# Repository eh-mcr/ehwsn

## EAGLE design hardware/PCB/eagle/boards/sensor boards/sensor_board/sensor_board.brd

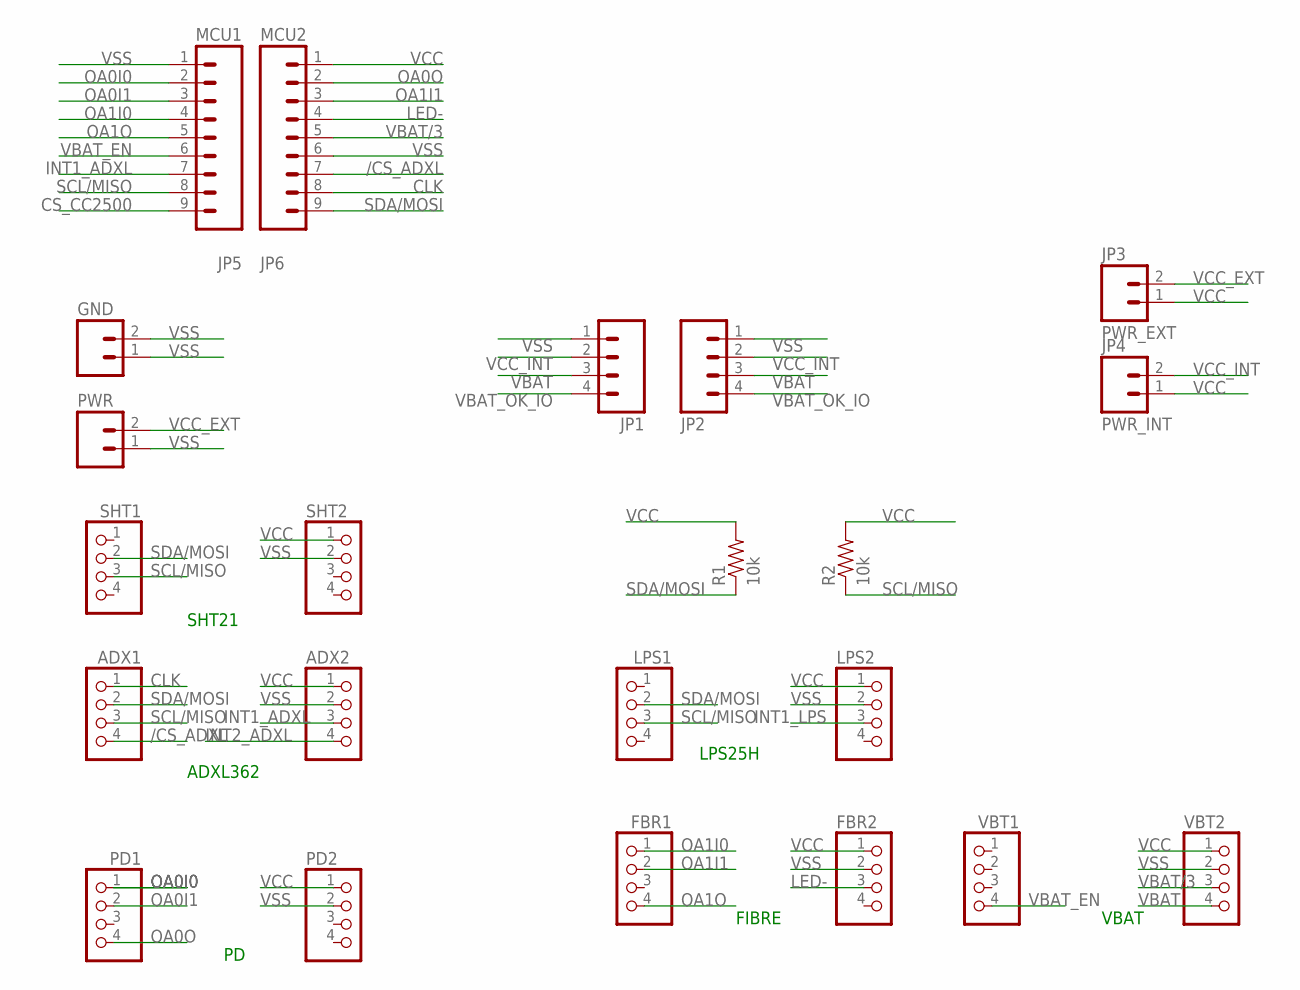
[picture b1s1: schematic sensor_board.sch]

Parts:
ADX1, ADX2: PINHD-1X4; 1X04
FBR1, FBR2: PINHD-1X4; 1X04
GND: M02PTH; 1X02
JP1, JP2: M04PTH; 1X04
JP3: PWR_EXT; 1X02
JP4: PWR_INT; 1X02
JP5: MCU1; 1X09
JP6: MCU2; 1X09
LPS1, LPS2: PINHD-1X4; 1X04
PD1, PD2: PINHD-1X4; 1X04
PWR: M02PTH; 1X02
R1, R2: 10k; AXIAL-0.3
SHT1, SHT2: PINHD-1X4; 1X04
VBT1, VBT2: PINHD-1X4; 1X04

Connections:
/CS_ADXL: ADX1.4, JP6.7
CLK: ADX1.1, JP6.8
CS_CC2500: JP5.9
INT1_ADXL: ADX2.3, JP5.7
INT1_LPS: LPS2.3
INT2_ADXL: ADX2.4
LED-: FBR2.3, JP6.4
OA0I0: JP5.2, PD1.1
OA0I1: JP5.3, PD1.2
OA0O: JP6.2, PD1.4
OA1I0: FBR1.1, JP5.4
OA1I1: FBR1.2, JP6.3
OA1O: FBR1.4, JP5.5
SCL/MISO: ADX1.3, JP5.8, LPS1.3, R2.P$1 (1), SHT1.3
SDA/MOSI: ADX1.2, JP6.9, LPS1.2, R1.P$1 (1), SHT1.2
VBAT: JP1.3, JP2.3, VBT2.4
VBAT/3: JP6.5, VBT2.3
VBAT_EN: JP5.6, VBT1.4
VBAT_OK_IO: JP1.4, JP2.4
VCC: ADX2.1, FBR2.1, JP3.1, JP4.1, JP6.1, LPS2.1, PD2.1, R1.P$2 (2), R2.P$2 (2), SHT2.1, VBT2.1
VCC_EXT: JP3.2, PWR.2
VCC_INT: JP1.2, JP2.2, JP4.2
VSS: ADX2.2, FBR2.2, GND.1, GND.2, JP1.1, JP2.1, JP5.1, JP6.6, LPS2.2, PD2.2, PWR.1, SHT2.2, VBT2.2

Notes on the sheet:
ADXL362
SHT21
LPS25H
FIBRE
VBAT

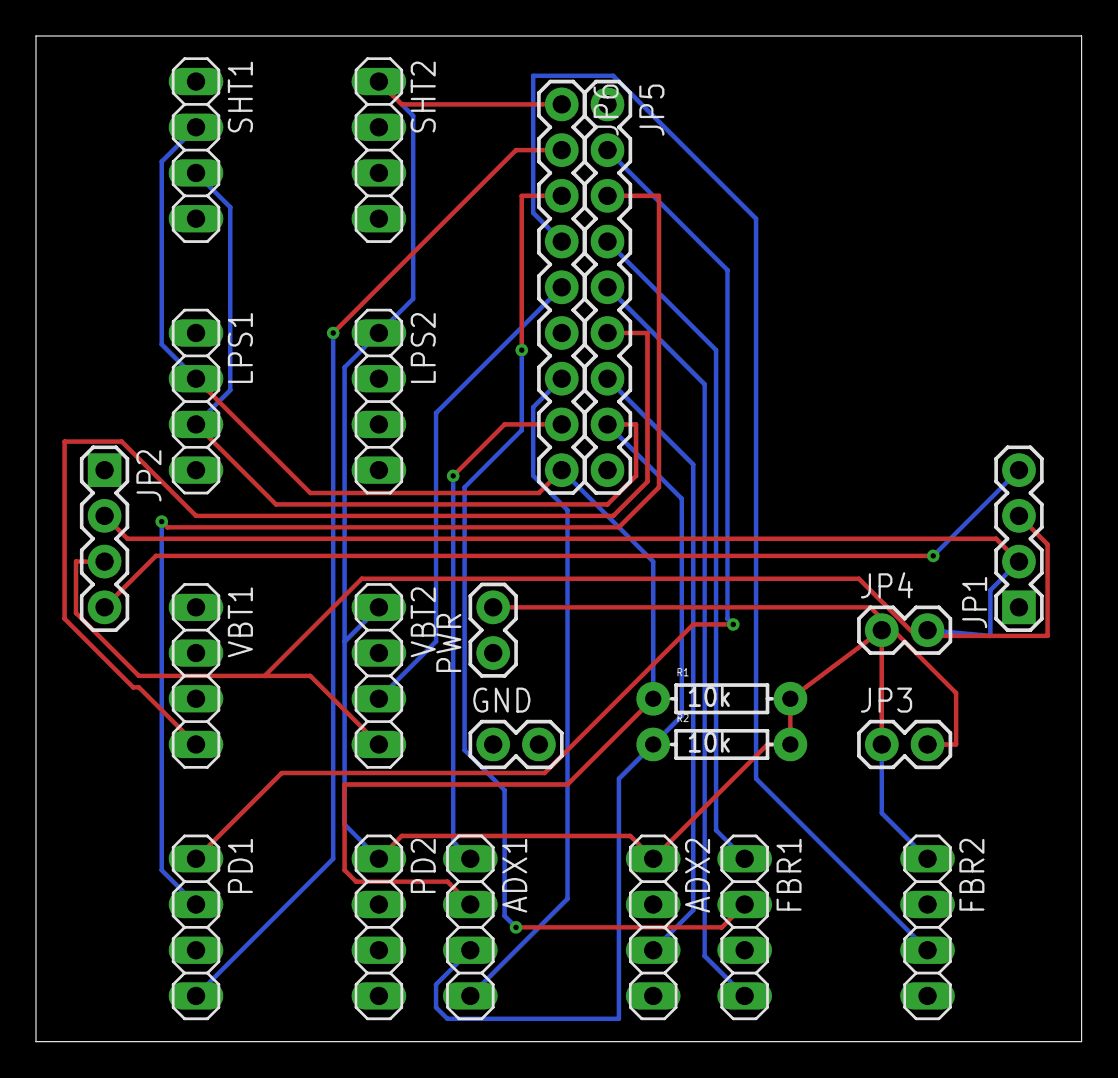
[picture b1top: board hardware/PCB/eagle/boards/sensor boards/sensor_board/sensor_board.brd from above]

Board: 2 copper layers, 58.1 x 55.9 mm, 22 parts (0 on the bottom side), 20 nets.

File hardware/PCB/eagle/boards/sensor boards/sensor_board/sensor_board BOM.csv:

"Qty","Value","Device","Package","Parts","Description","PROD_ID","VALUE",
"4","","M02PTH","1X02","GND, PWR, PWR_EXT, PWR_INT","Standard 2-pin 0.1" header. Use with","","",
"2","","M04PTH","1X04","JP1, JP2","Header 4","","",
"2","","M09","1X09","MCU1, MCU2","Header 9","","",
"12","","PINHD-1X4","1X04","ADX1, ADX2, FBR1, FBR2, LPS1, LPS2, PD1, PD2, SHT1, SHT2, VBT1, VBT2","PIN HEADER","","",
"2","10k","10KOHM-1/4W5%(PTH)","AXIAL-0.3","R1, R2","RES-09435","RES-9435","10k",

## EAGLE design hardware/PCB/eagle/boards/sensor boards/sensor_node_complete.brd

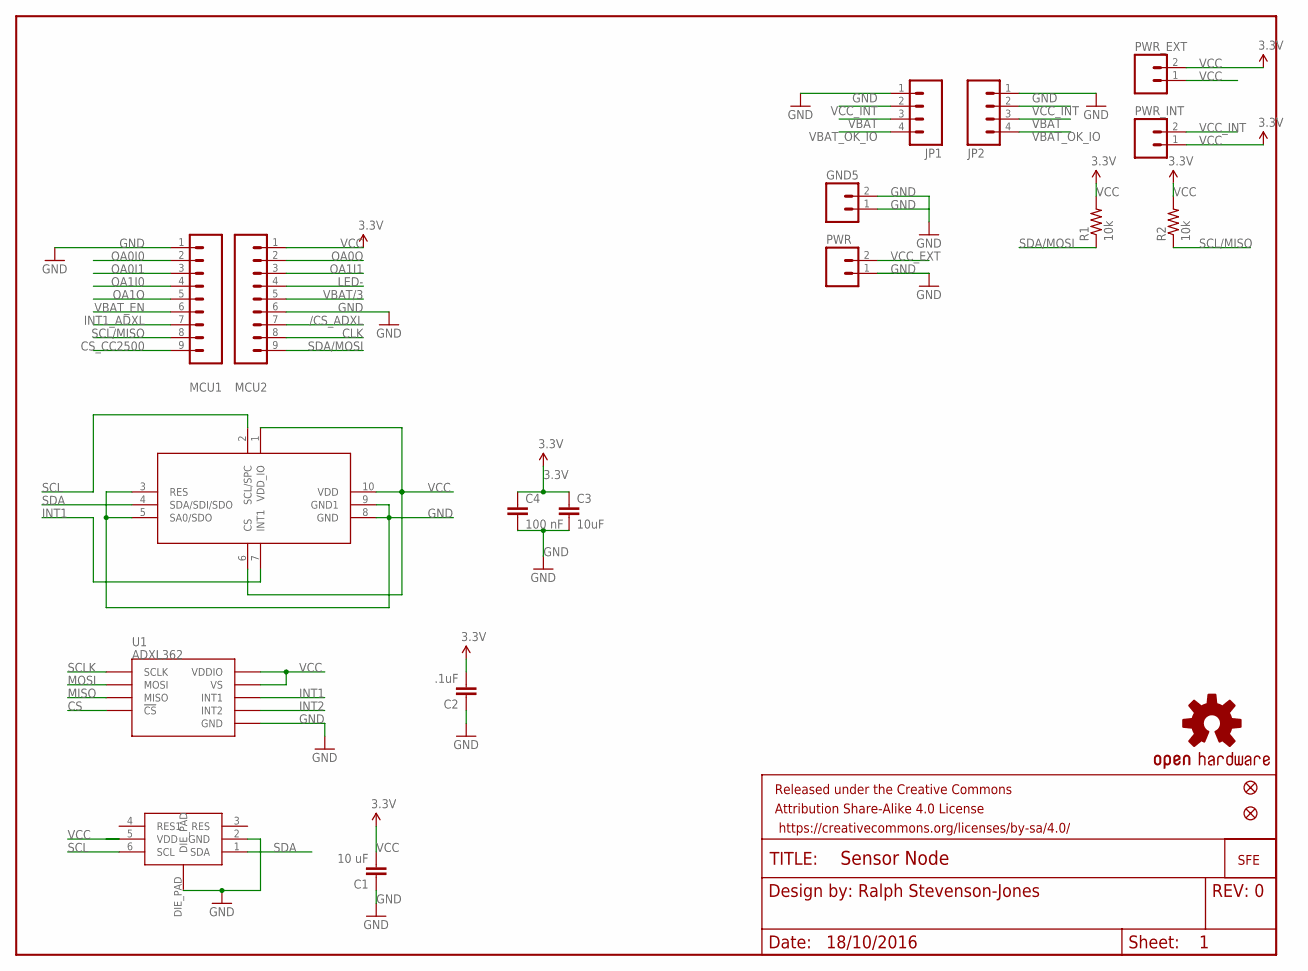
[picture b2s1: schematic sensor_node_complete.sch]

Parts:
C1: 10 uF; 0805-CAP
C2: .1uF; 0402-CAP
C3: 10uF; 0805-CAP
C4: 100 nF; 0805-CAP
FRAME1: FRAME-LETTER; CREATIVE_COMMONS
GND5: M02PTH; 1X02
JP1, JP2: M04PTH; 1X04
JP3: LOGO-SFESK; SFE-LOGO-FLAME
JP4, JP5: FIDUCIALUFIDUCIAL; MICRO-FIDUCIAL
MCU1, MCU2: M09; 1X09
PWR: M02PTH; 1X02
PWR_EXT: M02PTH; 1X02
PWR_INT: M02PTH; 1X02
R1, R2: 10k; 0805-RES
U1: ADXL362
U$1: SHT21!; SHT21
U$2: OSHW-LOGOS; OSHW-LOGO-S
U$3: LPS25HLPS25H; LPS25H

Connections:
3.3V: C3.1, C4.1
/CS_ADXL: MCU2.7
CLK: MCU2.8
CS: U1.P$8 (!CS)
CS_CC2500: MCU1.9
GND: C1.1, C2.1, C3.2, C4.2, GND5.1, GND5.2, JP1.1, JP2.1, MCU1.1, MCU2.6, PWR.1, U1.P$12 (GND), U1.P$13 (GND), U1.P$16 (GND), U$1.2 (GND), U$1.DIE_PAD, U$3.3 (RES), U$3.5 (SA0/SDO), U$3.8 (GND), U$3.9 (GND1)
INT1: U1.P$11 (INT1), U$3.7 (INT1)
INT1_ADXL: MCU1.7
INT2: U1.P$9 (INT2)
LED-: MCU2.4
MISO: U1.P$7 (MISO)
MOSI: U1.P$6 (MOSI)
OA0I0: MCU1.2
OA0I1: MCU1.3
OA0O: MCU2.2
OA1I0: MCU1.4
OA1I1: MCU2.3
OA1O: MCU1.5
SCL: U$1.6 (SCL), U$3.2 (SCL/SPC)
SCL/MISO: MCU1.8, R2.1
SCLK: U1.P$4 (SCLK)
SDA: U$1.1 (SDA), U$3.4 (SDA/SDI/SDO)
SDA/MOSI: MCU2.9, R1.1
VBAT: JP1.3, JP2.3
VBAT/3: MCU2.5
VBAT_EN: MCU1.6
VBAT_OK_IO: JP1.4, JP2.4
VCC: C1.2, C2.2, MCU2.1, PWR_EXT.1, PWR_EXT.2, PWR_INT.1, R1.2, R2.2, U1.P$1 (VDDIO), U1.P$14 (VS), U$1.5 (VDD), U$3.1 (VDD_IO), U$3.6 (CS), U$3.10 (VDD)
VCC_EXT: PWR.2
VCC_INT: JP1.2, JP2.2, PWR_INT.2

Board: 2 copper layers, 22 parts (0 on the bottom side), 11 nets, no tracks yet.

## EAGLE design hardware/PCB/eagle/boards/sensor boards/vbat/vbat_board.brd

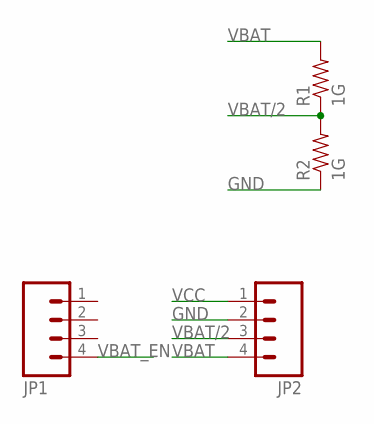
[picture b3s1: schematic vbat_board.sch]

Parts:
JP1, JP2: M04PTH; 1X04
R1, R2: 1G; TH_0.3-RES

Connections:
GND: JP2.2, R2.P$1 (1)
VBAT: JP2.4, R1.P$2 (2)
VBAT/2: JP2.3, R1.P$1 (1), R2.P$2 (2)
VBAT_EN: JP1.4
VCC: JP2.1

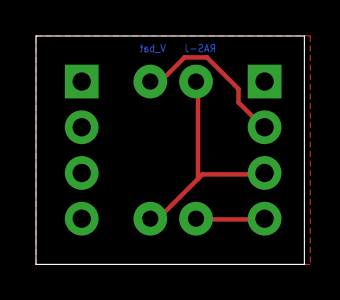
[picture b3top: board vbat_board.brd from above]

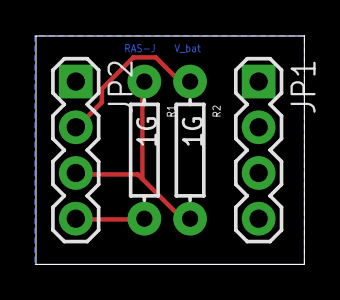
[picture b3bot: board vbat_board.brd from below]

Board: 2 copper layers, 14.9 x 12.7 mm, 4 parts (4 on the bottom side), 3 nets.

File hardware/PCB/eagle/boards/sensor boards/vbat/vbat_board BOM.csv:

"Qty","Value","Device","Package","Parts","Description","",
"2","","M04PTH","1X04","JP1, JP2","Header 4","",
"2","1G","RESISTORAXIAL-0.3","AXIAL-0.3","R1, R2","Resistor","",

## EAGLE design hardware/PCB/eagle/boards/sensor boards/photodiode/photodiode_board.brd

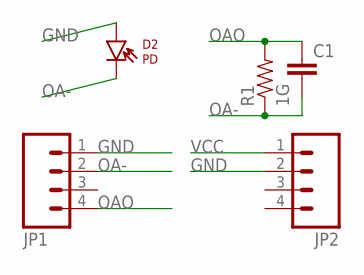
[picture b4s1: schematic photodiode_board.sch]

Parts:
C1: CAPTH_0.1-CAP; TH_0.1-CAP
D2: PD; TH_0.1-PD
JP1, JP2: M04PTH; 1X04
R1: 1G; TH_0.3-RES

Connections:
GND: D2.A, JP1.1, JP2.2
OA-: C1.2, D2.C, JP1.2, R1.P$1 (1)
OAO: C1.1, JP1.4, R1.P$2 (2)
VCC: JP2.1

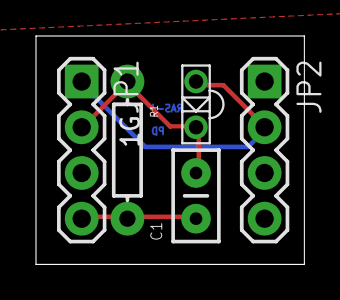
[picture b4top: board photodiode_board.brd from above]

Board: 2 copper layers, 14.9 x 12.7 mm, 5 parts (0 on the bottom side), 3 nets.

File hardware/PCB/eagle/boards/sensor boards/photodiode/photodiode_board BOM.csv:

Qty,Value,Device,Package,Parts,Description
1,,CAPPTH,CAP-PTH-SMALL,C1,Capacitor
2,,M04PTH,1X04,"JP1, JP2",Header 4
1,1G,RESISTORAXIAL-0.3,AXIAL-0.3,R1,Resistor
1,PD,LTE-302,LTE-302,D2,Through-hole side-firing 940nm IR LED

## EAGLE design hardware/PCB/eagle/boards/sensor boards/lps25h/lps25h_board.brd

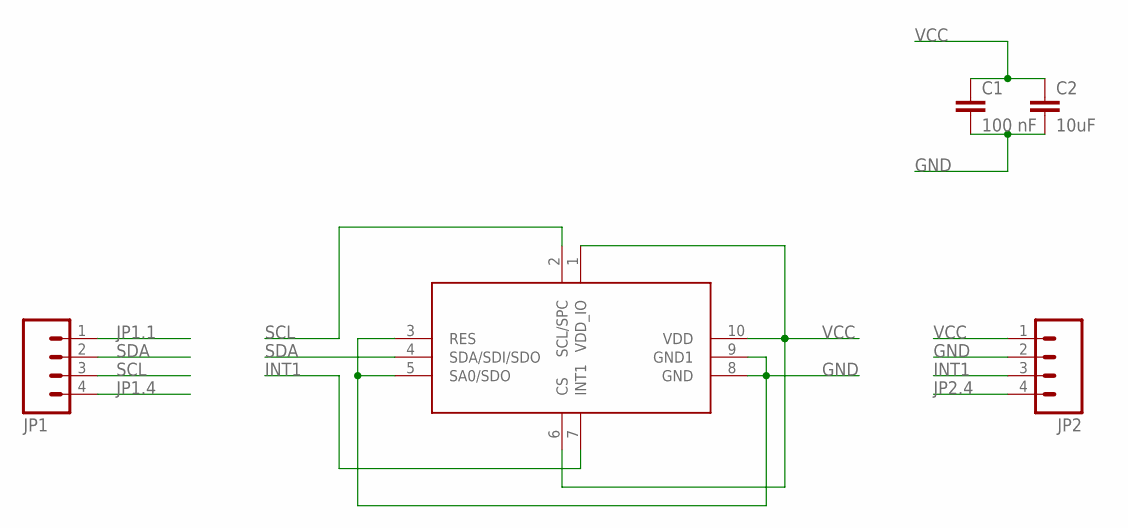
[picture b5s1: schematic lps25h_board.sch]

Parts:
C1: 100 nF; 0805-CAP
C2: 10uF; 0805-CAP
JP1, JP2: M04PTH; 1X04
U$1: LPS25HLPS25H; LPS25H

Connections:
GND: C1.2, C2.2, JP2.2, U$1.3 (RES), U$1.5 (SA0/SDO), U$1.8 (GND), U$1.9 (GND1)
INT1: JP2.3, U$1.7 (INT1)
JP1.1: JP1.1
JP1.4: JP1.4
JP2.4: JP2.4
SCL: JP1.3, U$1.2 (SCL/SPC)
SDA: JP1.2, U$1.4 (SDA/SDI/SDO)
VCC: C1.1, C2.1, JP2.1, U$1.1 (VDD_IO), U$1.6 (CS), U$1.10 (VDD)

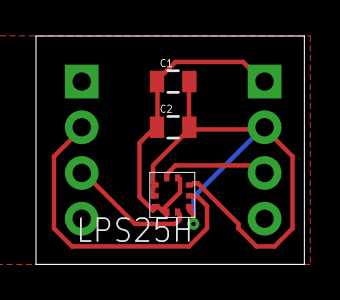
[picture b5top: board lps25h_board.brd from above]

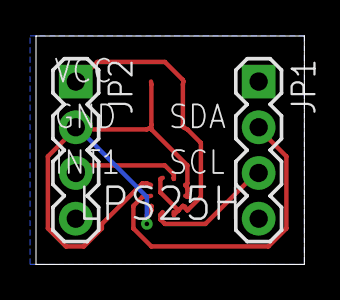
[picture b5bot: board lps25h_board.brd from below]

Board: 2 copper layers, 14.9 x 12.7 mm, 5 parts (2 on the bottom side), 5 nets.

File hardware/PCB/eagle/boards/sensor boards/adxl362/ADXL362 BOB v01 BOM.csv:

"Qty","Value","Device","Package","Parts","Description","PROD_ID",
"2","","M04PTH","1X04","JP1, JP2","Header 4","",
"1",".1uF","CAP0402-CAP","0402-CAP","C1","Capacitor","CAP-00810",
"1","ADXL362","ADXL362","ADXL362","U1","Micropower 3-axis accelerometer","",
"2","FIDUCIALUFIDUCIAL","FIDUCIALUFIDUCIAL","MICRO-FIDUCIAL","JP4, JP5","Fiducial Alignment Points","",
"1","FRAME-LETTER","FRAME-LETTER","CREATIVE_COMMONS","FRAME1","Schematic Frame","",
"1","LOGO-SFESK","LOGO-SFESK","SFE-LOGO-FLAME","JP3","Spark Fun Electronics PCB Logo","",
"1","OSHW-LOGOS","OSHW-LOGOS","OSHW-LOGO-S","U$1","Open Source Hardware Logo This logo indicates the piece of hardware it is found on incorporates a OSHW license and/or adheres to the definition of open source hardware found here: http://freedomdefined.org/OSHW","",

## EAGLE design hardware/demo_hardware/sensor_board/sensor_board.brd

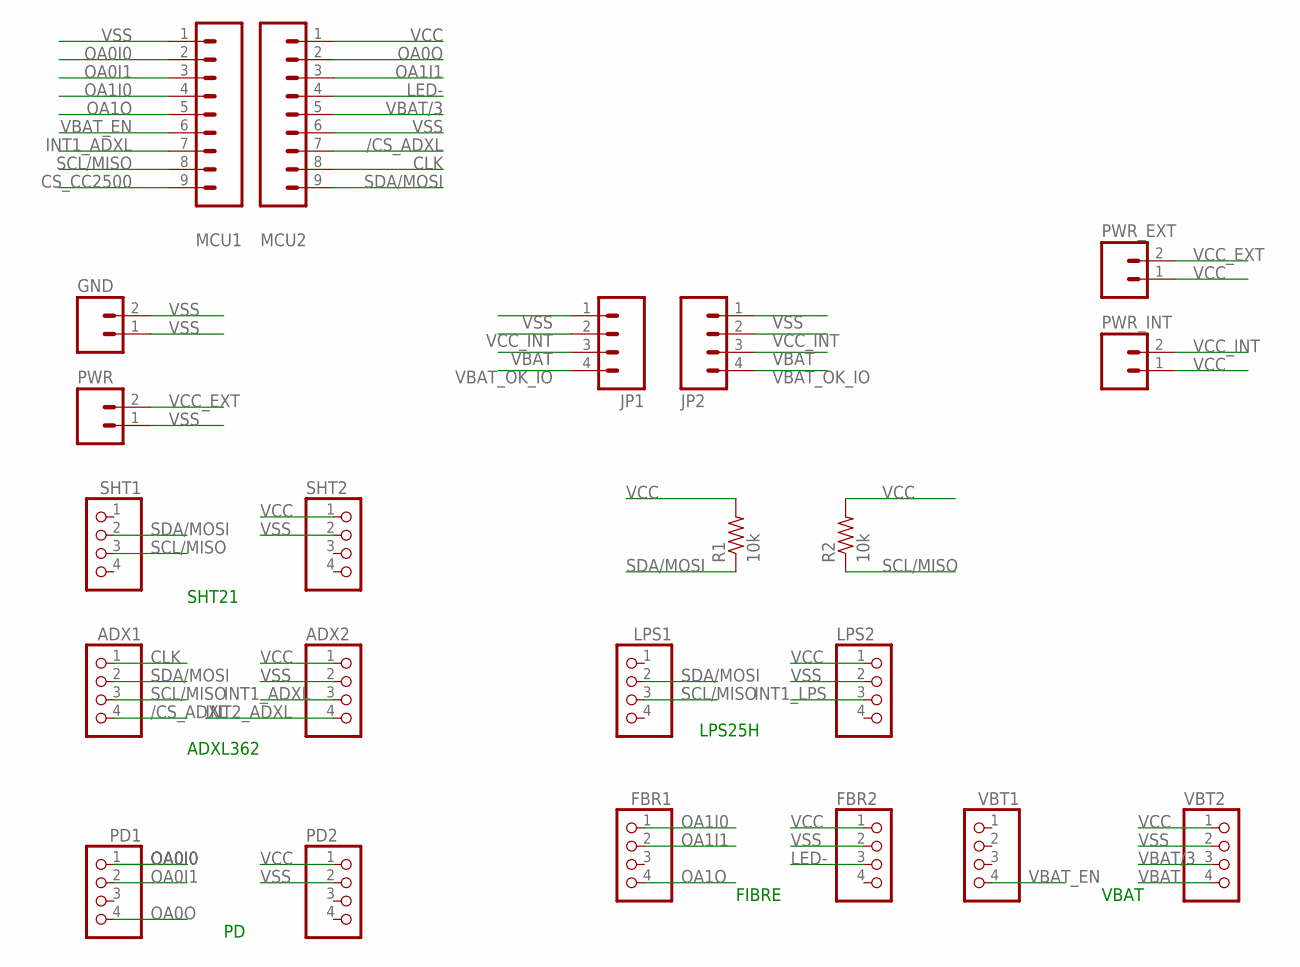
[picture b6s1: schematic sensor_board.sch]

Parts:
ADX1, ADX2: PINHD-1X4; 1X04
FBR1, FBR2: PINHD-1X4; 1X04
GND: M02PTH; 1X02
JP1, JP2: M04PTH; 1X04
LPS1, LPS2: PINHD-1X4; 1X04
MCU1, MCU2: M09; 1X09
PD1, PD2: PINHD-1X4; 1X04
PWR: M02PTH; 1X02
PWR_EXT: M02PTH; 1X02
PWR_INT: M02PTH; 1X02
R1, R2: 10k; AXIAL-0.3
SHT1, SHT2: PINHD-1X4; 1X04
VBT1, VBT2: PINHD-1X4; 1X04

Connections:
/CS_ADXL: ADX1.4, MCU2.7
CLK: ADX1.1, MCU2.8
CS_CC2500: MCU1.9
INT1_ADXL: ADX2.3, MCU1.7
INT1_LPS: LPS2.3
INT2_ADXL: ADX2.4
LED-: FBR2.3, MCU2.4
OA0I0: MCU1.2, PD1.1
OA0I1: MCU1.3, PD1.2
OA0O: MCU2.2, PD1.4
OA1I0: FBR1.1, MCU1.4
OA1I1: FBR1.2, MCU2.3
OA1O: FBR1.4, MCU1.5
SCL/MISO: ADX1.3, LPS1.3, MCU1.8, R2.P$1 (1), SHT1.3
SDA/MOSI: ADX1.2, LPS1.2, MCU2.9, R1.P$1 (1), SHT1.2
VBAT: JP1.3, JP2.3, VBT2.4
VBAT/3: MCU2.5, VBT2.3
VBAT_EN: MCU1.6, VBT1.4
VBAT_OK_IO: JP1.4, JP2.4
VCC: ADX2.1, FBR2.1, LPS2.1, MCU2.1, PD2.1, PWR_EXT.1, PWR_INT.1, R1.P$2 (2), R2.P$2 (2), SHT2.1, VBT2.1
VCC_EXT: PWR.2, PWR_EXT.2
VCC_INT: JP1.2, JP2.2, PWR_INT.2
VSS: ADX2.2, FBR2.2, GND.1, GND.2, JP1.1, JP2.1, LPS2.2, MCU1.1, MCU2.6, PD2.2, PWR.1, SHT2.2, VBT2.2

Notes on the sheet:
ADXL362
SHT21
LPS25H
FIBRE
VBAT

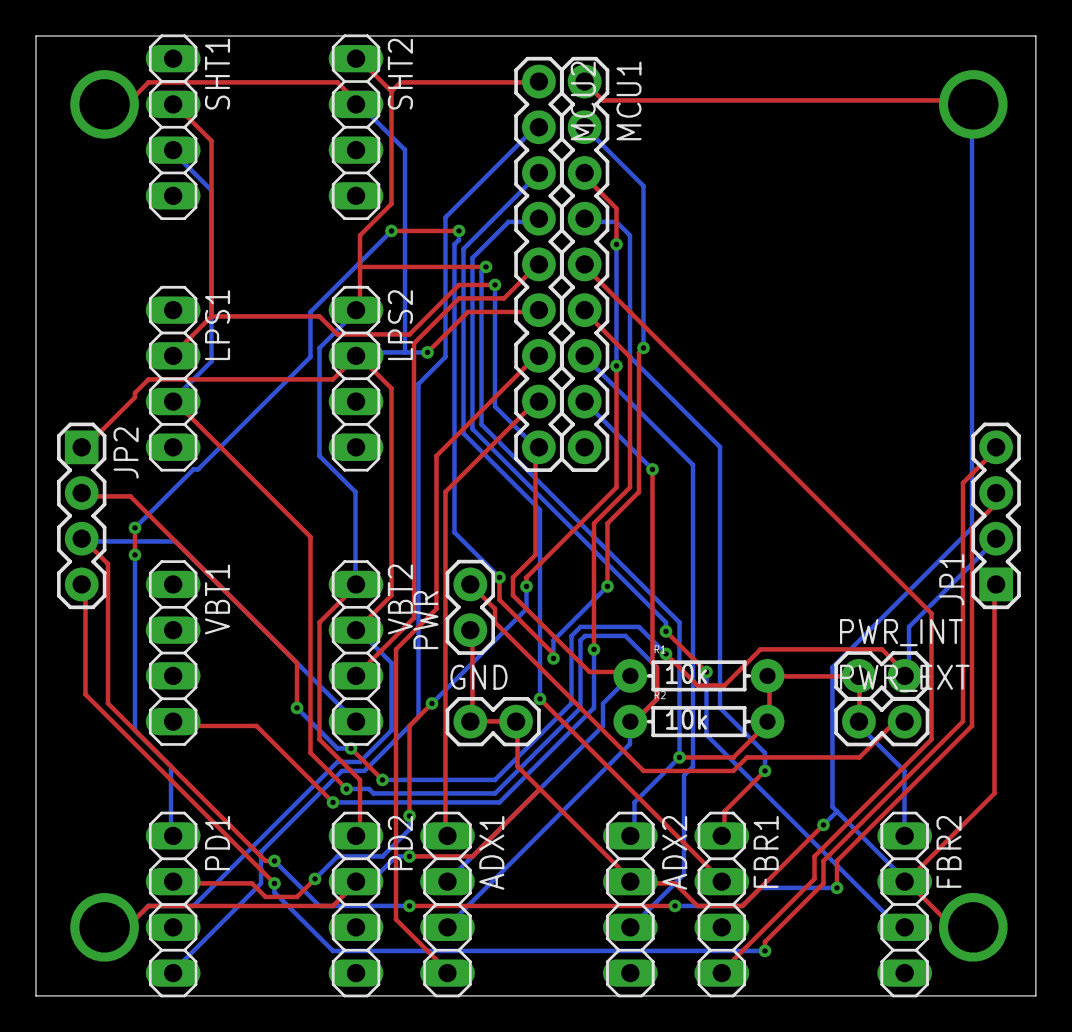
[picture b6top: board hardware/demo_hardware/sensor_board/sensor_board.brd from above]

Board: 2 copper layers, 55.5 x 53.3 mm, 22 parts (0 on the bottom side), 20 nets.

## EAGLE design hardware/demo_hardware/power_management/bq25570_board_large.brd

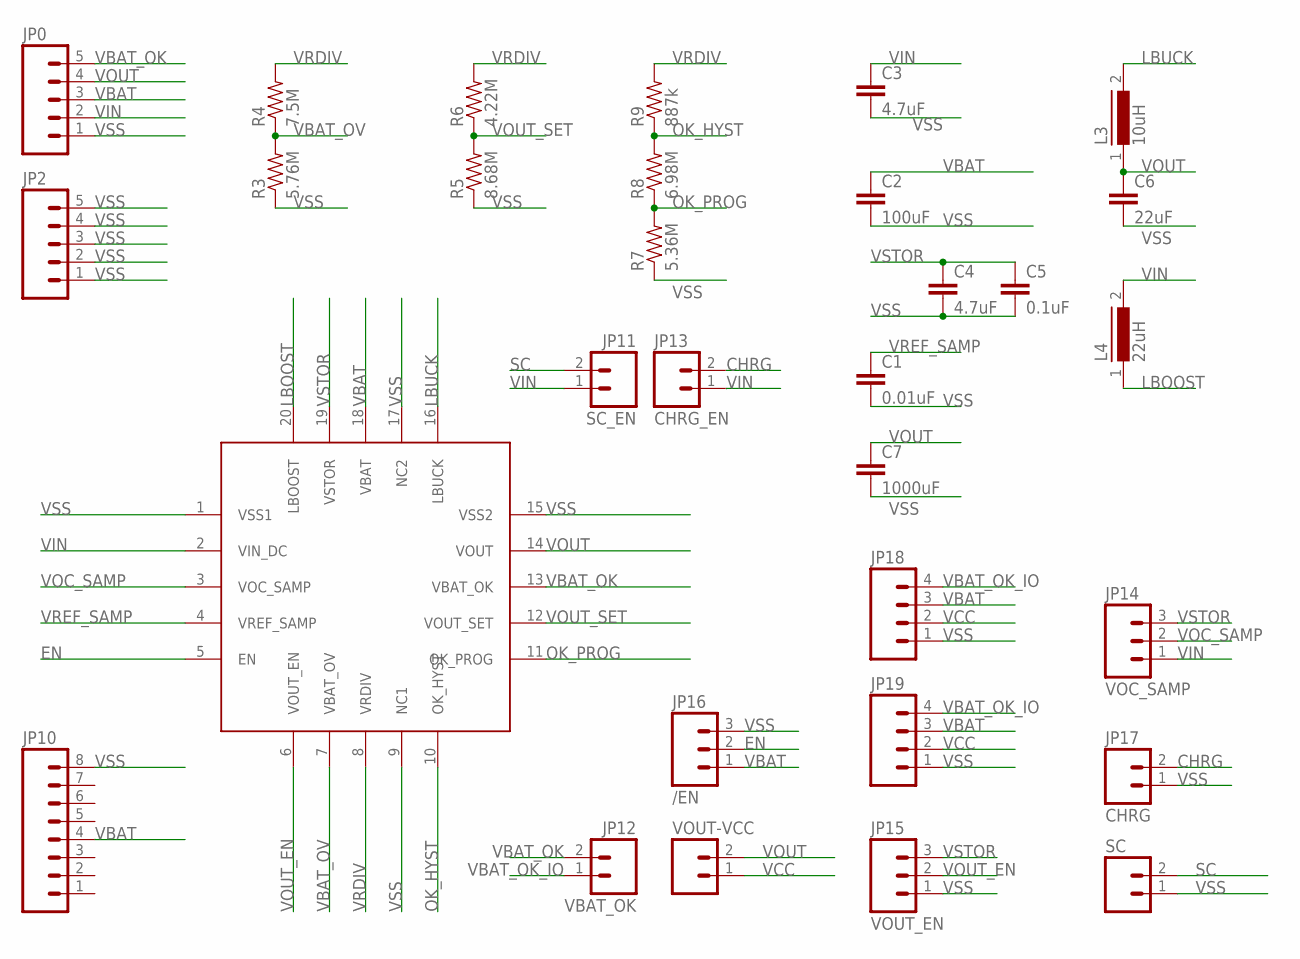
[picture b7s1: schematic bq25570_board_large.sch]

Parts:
C1: 0.01uF; CAP-PTH-SMALLEZ
C2: 100uF; CAP-PTH-SMALLEZ
C3, C4: 4.7uF; CAP-PTH-SMALLEZ
C5: 0.1uF; CAP-PTH-SMALLEZ
C6: 22uF; CAP-PTH-SMALLEZ
C7: 1000uF; CAP-PTH-SMALLEZ
JP0, JP2: M05PTH; 1X05
JP10: M08; 1X08_ROUND
JP11: SC_EN; 1X02
JP12: VBAT_OK; 1X02
JP13: CHRG_EN; 1X02
JP14: VOC_SAMP; 1X03
JP15: VOUT_EN; 1X03
JP16: /EN; 1X03
JP17: CHRG; 1X02
JP18, JP19: M04PTH; 1X04
L3: 10uH; BC12
L4: 22uH; BC12
R3: 5.76M; AXIAL-0.3
R4: 7.5M; AXIAL-0.3
R5: 8.68M; AXIAL-0.3
R6: 4.22M; AXIAL-0.3
R7: 5.36M; AXIAL-0.3
R8: 6.98M; AXIAL-0.3
R9: 887k; AXIAL-0.3
SC: M02PTH; 1X02
SV2: BQ25570_BOARD; MA05-1
VOUT-VCC: M02PTH; 1X02

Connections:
CHRG: JP13.2, JP17.2
EN: JP16.2, SV2.5 (EN)
LBOOST: L4.1, SV2.20 (LBOOST)
LBUCK: L3.2, SV2.16 (LBUCK)
OK_HYST: R8.P$2 (2), R9.P$1 (1), SV2.10 (OK_HYST)
OK_PROG: R7.P$2 (2), R8.P$1 (1), SV2.11 (OK_PROG)
SC: JP11.2, SC.2
VBAT: C2.1, JP0.3, JP10.4, JP16.1, JP18.3, JP19.3, SV2.18 (VBAT)
VBAT_OK: JP0.5, JP12.2, SV2.13 (VBAT_OK)
VBAT_OK_IO: JP12.1, JP18.4, JP19.4
VBAT_OV: R3.P$2 (2), R4.P$1 (1), SV2.7 (VBAT_OV)
VCC: JP18.2, JP19.2, VOUT-VCC.1
VIN: C3.1, JP0.2, JP11.1, JP13.1, JP14.1, L4.2, SV2.2 (VIN_DC)
VOC_SAMP: JP14.2, SV2.3 (VOC_SAMP)
VOUT: C6.1, C7.1, JP0.4, L3.1, SV2.14 (VOUT), VOUT-VCC.2
VOUT_EN: JP15.2, SV2.6 (VOUT_EN)
VOUT_SET: R5.P$2 (2), R6.P$1 (1), SV2.12 (VOUT_SET)
VRDIV: R4.P$2 (2), R6.P$2 (2), R9.P$2 (2), SV2.8 (VRDIV)
VREF_SAMP: C1.1, SV2.4 (VREF_SAMP)
VSS: C1.2, C2.2, C3.2, C4.2, C5.2, C6.2, C7.2, JP0.1, JP2.1, JP2.2, JP2.3, JP2.4, JP2.5, JP10.8, JP15.1, JP16.3, JP17.1, JP18.1, JP19.1, R3.P$1 (1), R5.P$1 (1), R7.P$1 (1), SC.1, SV2.1 (VSS1), SV2.9 (NC1), SV2.15 (VSS2), SV2.17 (NC2)
VSTOR: C4.1, C5.1, JP14.3, JP15.3, SV2.19 (VSTOR)

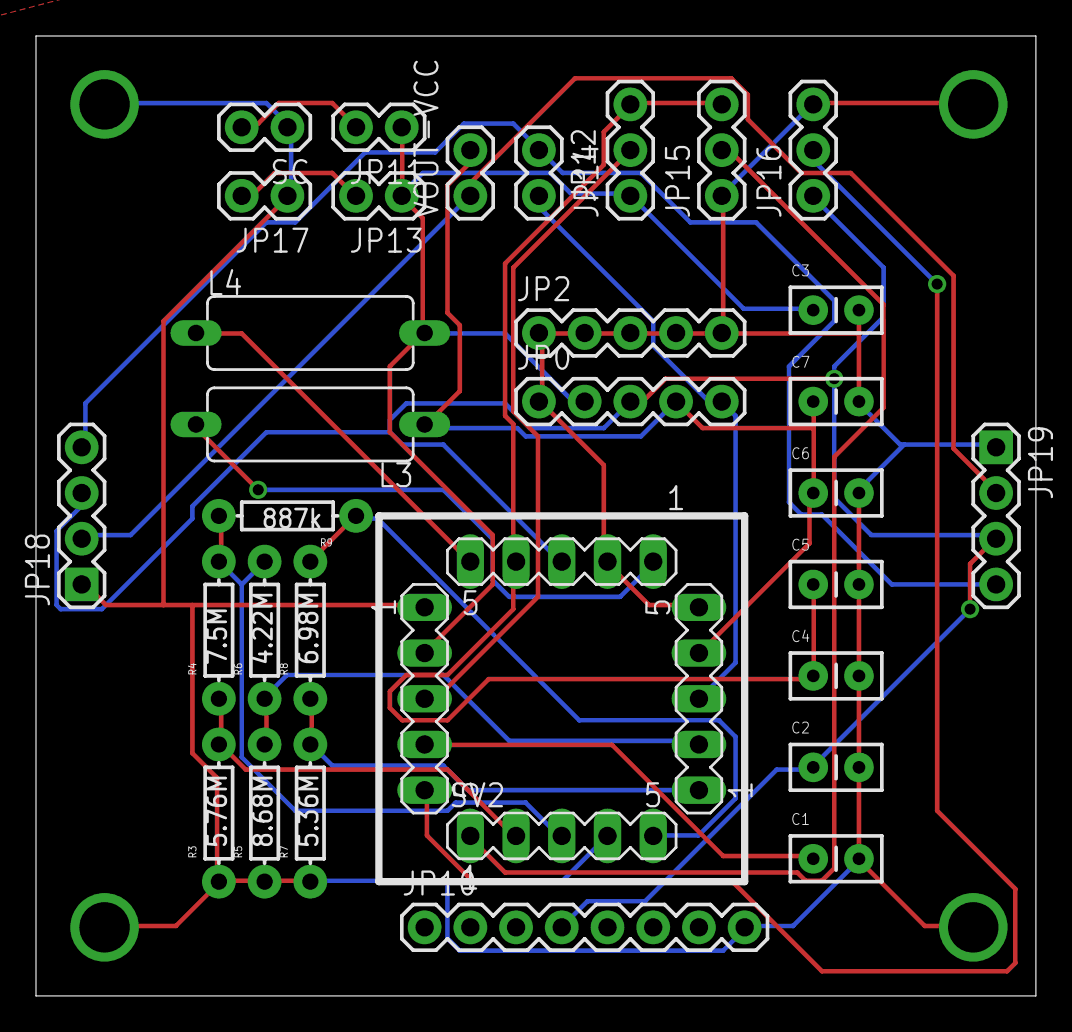
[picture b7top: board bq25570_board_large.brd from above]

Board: 2 copper layers, 55.5 x 53.3 mm, 31 parts (0 on the bottom side), 21 nets.

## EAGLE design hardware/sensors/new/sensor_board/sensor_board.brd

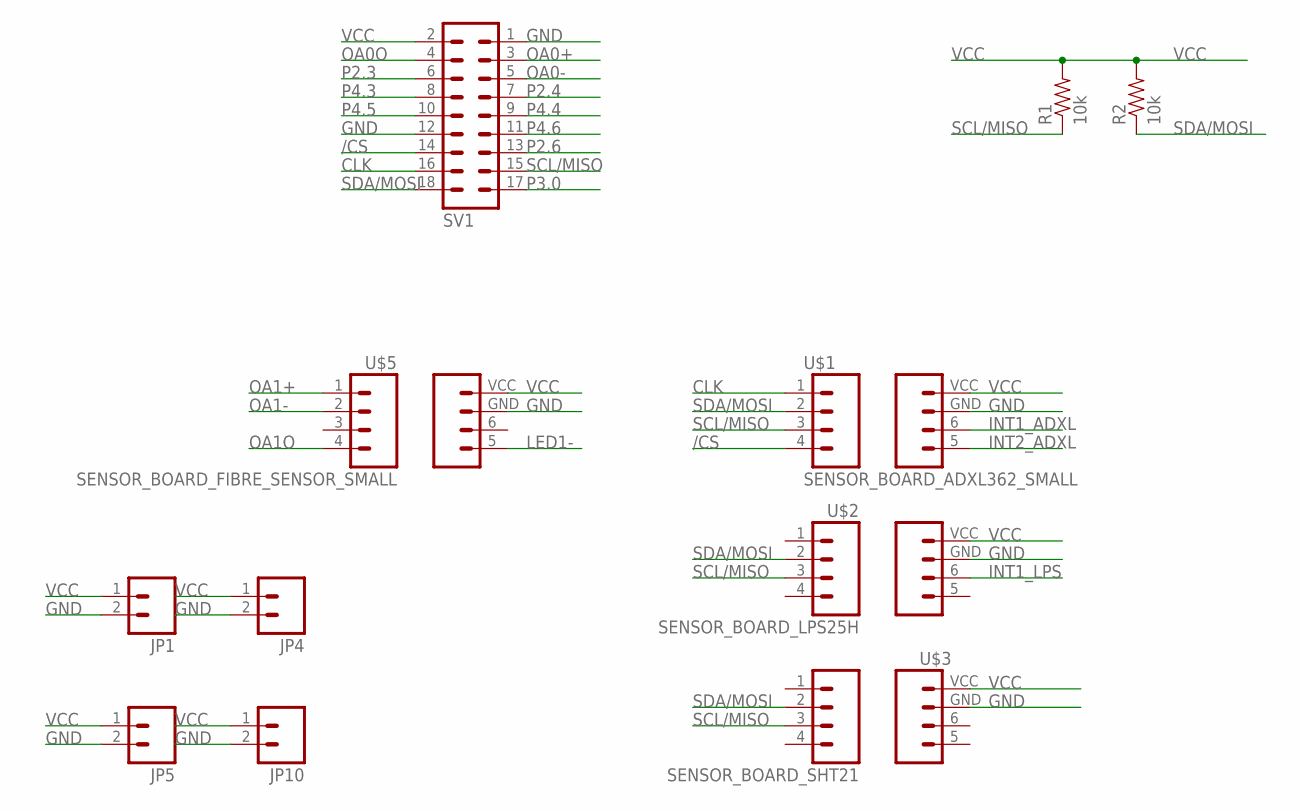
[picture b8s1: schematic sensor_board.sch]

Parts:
JP1, JP4, JP5, JP10: M02PTH; 1X02
R1, R2: 10k; AXIAL-0.3
SV1: MA09-2
U$1: SENSOR_BOARD_ADXL362_SMALL; SENSOR_BOARD_GEN_SMALL
U$2: SENSOR_BOARD_LPS25H; SENSOR_BOARD_GEN
U$3: SENSOR_BOARD_SHT21; SENSOR_BOARD_GEN
U$5: SENSOR_BOARD_FIBRE_SENSOR_SMALL; SENSOR_BOARD_GEN_SMALL

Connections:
/CS: SV1.14, U$1.4 (/CS)
CLK: SV1.16, U$1.1 (CLK)
GND: JP1.2, JP4.2, JP5.2, JP10.2, SV1.1, SV1.12, U$1.GND, U$2.GND, U$3.GND, U$5.GND
INT1_ADXL: U$1.6 (INT1)
INT1_LPS: U$2.6 (INT1)
INT2_ADXL: U$1.5 (INT2)
LED1-: U$5.5 (LED-)
OA0+: SV1.3
OA0-: SV1.5
OA0O: SV1.4
OA1+: U$5.1 (OA+)
OA1-: U$5.2 (OA-)
OA1O: U$5.4 (OAO)
P2.3: SV1.6
P2.4: SV1.7
P2.6: SV1.13
P3.0: SV1.17
P4.3: SV1.8
P4.4: SV1.9
P4.5: SV1.10
P4.6: SV1.11
SCL/MISO: R1.P$1 (1), SV1.15, U$1.3 (MISO), U$2.3 (SCL), U$3.3 (SCL)
SDA/MOSI: R2.P$1 (1), SV1.18, U$1.2 (MOSI), U$2.2 (SDA), U$3.2 (SDA)
VCC: JP1.1, JP4.1, JP5.1, JP10.1, R1.P$2 (2), R2.P$2 (2), SV1.2, U$1.VCC, U$2.VCC, U$3.VCC, U$5.VCC

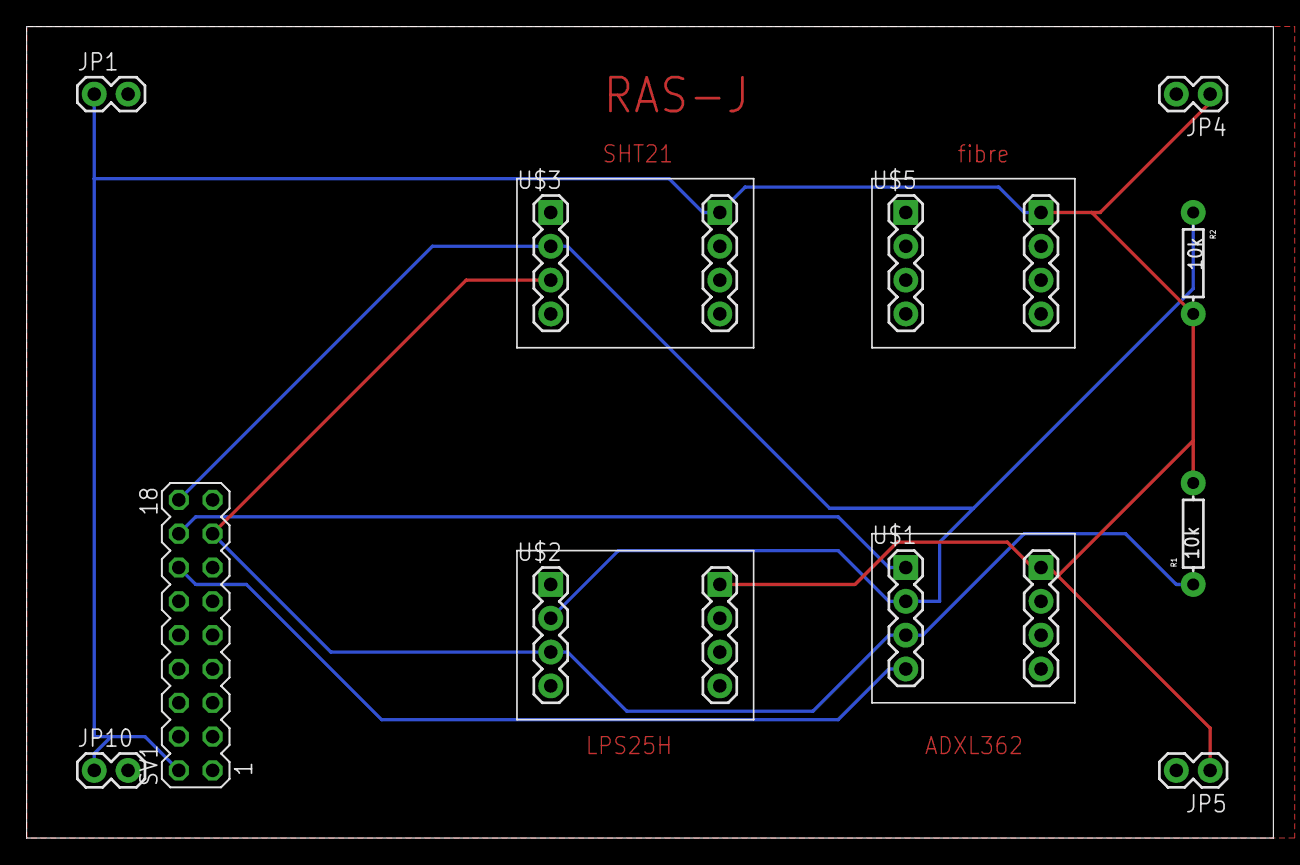
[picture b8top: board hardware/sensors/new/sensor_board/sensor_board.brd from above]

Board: 2 copper layers, 93.7 x 61.0 mm, 11 parts (0 on the bottom side), 6 nets.

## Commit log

2016-07-25 Files added to project
    Files added for sensor network demo version
2016-07-25 Added hardware folder
2016-07-25 Updated Components folder
    Previously errors were occuring during compilation within mrfi fils.
    Copied over original Components folder
2016-07-25 Added macros file
    macors.ini is used to define file paths e.g. for include functions
2016-07-25 Created comms libraries
    Created spi, usci and sht21 library files. Added the folders to the
    project include path (defined within .cproject file)
2016-07-26 Updated sensor libraries
    Updated ADXL362, PD, OA and ADC libraries. Moved functions to general
    header/source files. Added NodeStatus and InterruptSource flags
2016-10-15 Transferred ownership to eh-mcr
2016-10-15 deleted old files
2016-10-15 added readme to hardware
    to populate with description of boards
2016-10-17 Added boards
    - PCB files added to folders
    - eagle file added
2016-10-17 added component libraries and BOM
2016-10-17 add components
2016-10-18 Added accelerometer board
2016-10-18 added sht21 board
2016-10-18 added eagle libraries
2016-10-18 added complete board
2016-10-18 updated boards with new components
2016-10-20 Updated BQ25570 shield
2016-10-20 Created BQ25570 3D
    - created EagleUp files from PCB
    - created BQ25570_BOARD.skp in sketchup folder
2016-10-20 Updated pm board
    - updated power_management_board PCB
2016-10-20 Pm board - sketchup
    - created eagleup files to power_management_board
    - created skethup POWER_MANAGEMENT_BOARD.skp
2016-10-20 Updated libraries
    - updated integrated_circuits.lbr
2016-10-20 Updated libraries
    - updated passive_components.lbr
2016-10-20 Created BQ25570 model
    Created BQ25570.skp
2016-10-21 Increase visibility of pm board
    - increased spacing between components in the power management board to
    increase visibility of labels and values in silk screen
2016-10-21 adjusted spacing on sensor board
    - increased the spacing between components on the sensor board to aid
    visibility of the values and names on the board
2016-10-21 updated bq25570 shield
    - updated the BQ25570 shield in the sensor shields library
    - printed out schematic of the shield
2016-11-01 updated eagle library links

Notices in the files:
parts and their libraries:
SparkFun-Capacitors: Licensing: Creative Commons ShareAlike 4.0 International - https://creativecommons.org/licenses/by-sa/4.0
SparkFun-Passives: Licensing: CC v3.0 Share-Alike You are welcome to use this library for commercial purposes.
SparkFun-Aesthetics: Released under the Creative Commons
